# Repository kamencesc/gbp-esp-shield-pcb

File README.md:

# Game Boy WiFi Printer - WEMOS D1 Mini Shield

Enthusiasts on the [Game Boy Camera Club discord server](http://bit.ly/gbccd) have been working on a Game Boy Printer emulator project based on ESP8266 D1 mini boards. Taking inspiration from other projects like the [Gameboy Link Cable Breakout PCB](https://github.com/Palmr/gb-link-cable), I created this shield board to add a link connector and pinouts for an oled screen.

The board is redesigned to a nearly size of a WEMOS D1 mini. ~~There's a pinout for a 128x32 OLED with configurable GND and VCC.~~

Here's a render of the PCB (OSH-Park):

You can get help with the original project and find info on the software that runs on the ESP by joining the [Game Boy Camera Club discord server](http://bit.ly/gbccd)

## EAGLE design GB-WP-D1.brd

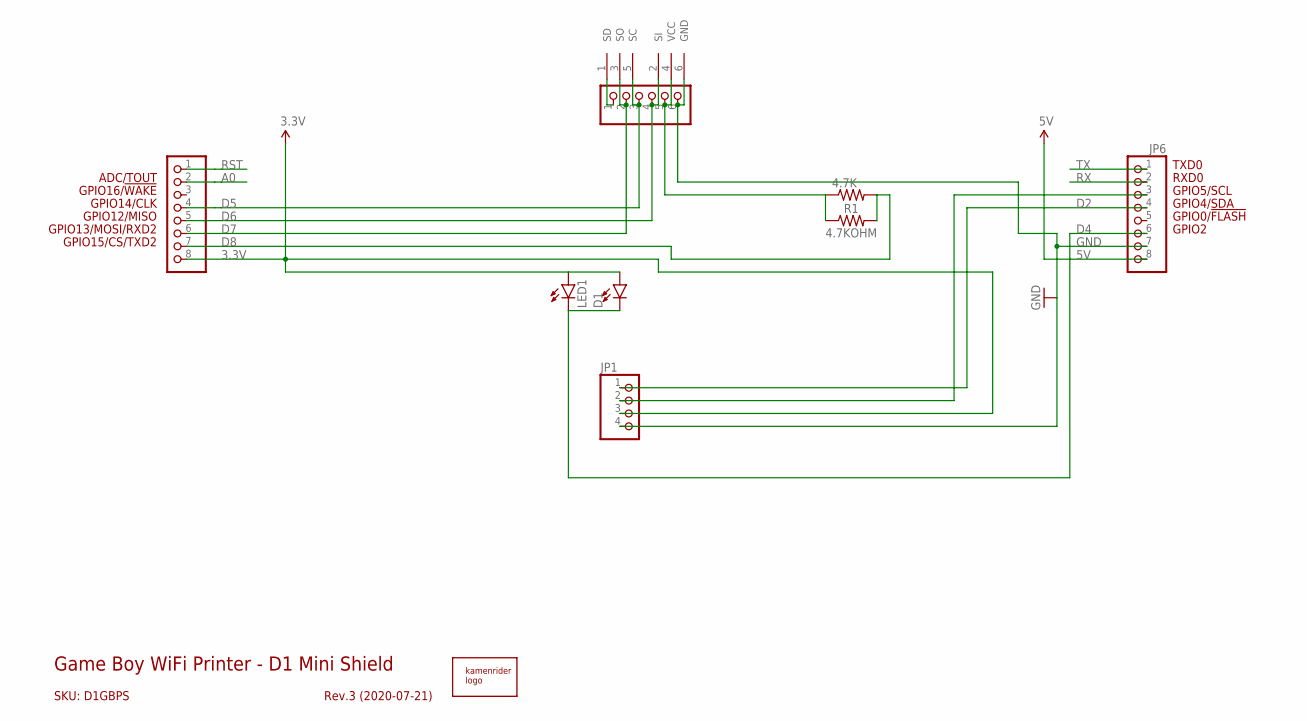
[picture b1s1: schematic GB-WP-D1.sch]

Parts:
4.7K: R-US_0207/10; 0207/10
D1: LED1206; LED-1206
JP1: PINHD-1X4/OCT; 1X04/OCT
JP3, JP6: PINHD-1X8/OCT; 1X08/OCT
JP4: PINHD-1X6/OCT; 1X06/OCT
LED1: LED3MM
R1: 4.7KOHM; 1206
U$2: GB-LINK-PADS; GB-LINK-PCB
U$3: KAMENRIDER_LOGOV2_COLOR_OPAC; 10_6_V2

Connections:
3.3V: D1.A, JP1.3, JP3.8, LED1.A
5V: JP6.8
A0: JP3.2
D2: JP1.1, JP6.4
D4: D1.C, JP6.6, LED1.K (C)
D5: JP3.4, JP4.3, U$2.5 (SC)
D6: JP3.5, JP4.4, U$2.2 (SI)
D7: JP3.6, JP4.2, U$2.3 (SO)
D8: 4.7K.2, JP3.7, R1.2
GND: JP1.4, JP4.6, JP6.7, U$2.6 (GND)
unnamed: JP4.1, U$2.1 (SD)
unnamed: 4.7K.1, JP4.5, R1.1, U$2.4 (VCC)
unnamed: JP1.2, JP6.3
RST: JP3.1
RX: JP6.2
TX: JP6.1

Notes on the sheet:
GPIO2
GPIO0/!FLASH
GPIO12/MISO
GPIO4/SDA
GPIO5/SCL
RXD0
TXD0
GPIO13/MOSI/RXD2
GPIO14/CLK
GPIO15/CS/TXD2
GPIO16/!WAKE
SKU: D1GBPS
Game Boy WiFi Printer - D1 Mini Shield
Rev.3 (2020-07-21)
ADC/TOUT

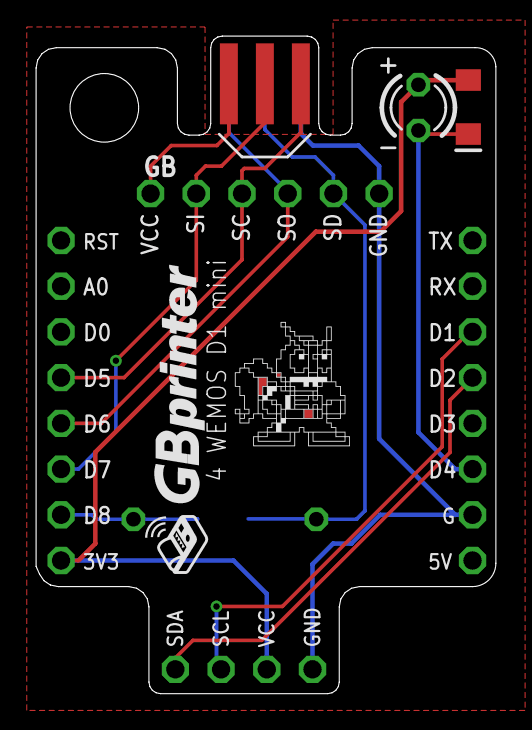
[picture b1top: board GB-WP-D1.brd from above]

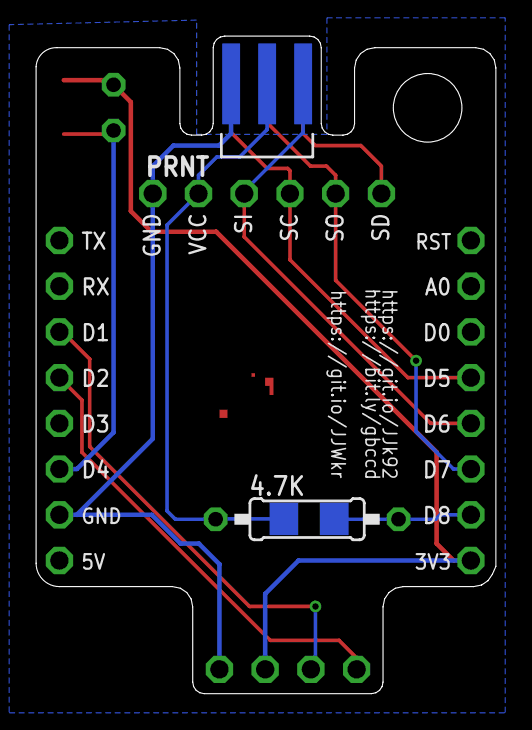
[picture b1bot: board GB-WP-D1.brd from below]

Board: 2 copper layers, 25.5 x 36.5 mm, 10 parts (2 on the bottom side), 11 nets.

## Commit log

2020-07-21 Add files via upload
    WEMOS D1 mini size
2020-07-21 Add files via upload
    Added optional SMD 1206 fotprint for resistor and LED
2020-07-21 Add files via upload
    new render
2020-07-22 Add files via upload
    Minor changes on design
2020-07-22 Add files via upload
    GND layers
2020-09-07 Add files via upload
    SMT Jumpers for the OLED's GND and VCC
2020-10-28 Add files via upload
    Unnecesari SMT Jumper config for OLED 128x32
2020-10-28 Add files via upload
    Preview update

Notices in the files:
parts and their libraries:
SparkFun-LED: Licensing: Creative Commons ShareAlike 4.0 International - https://creativecommons.org/licenses/by-sa/4.0
freetronics-original: Licensing: CC v3.0 Share-Alike You are welcome to use this library for commercial purposes.
